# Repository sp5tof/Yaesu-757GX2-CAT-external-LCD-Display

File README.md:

# Yaesu-757GX2-CAT-external-LCD-Display
External HD77480 LCD display which shows up the transceiver status.
Arduino code, 3D case ready to print, Eagle schematic & board.
More Informations you can find at http://sp5tof.qrz.pl .

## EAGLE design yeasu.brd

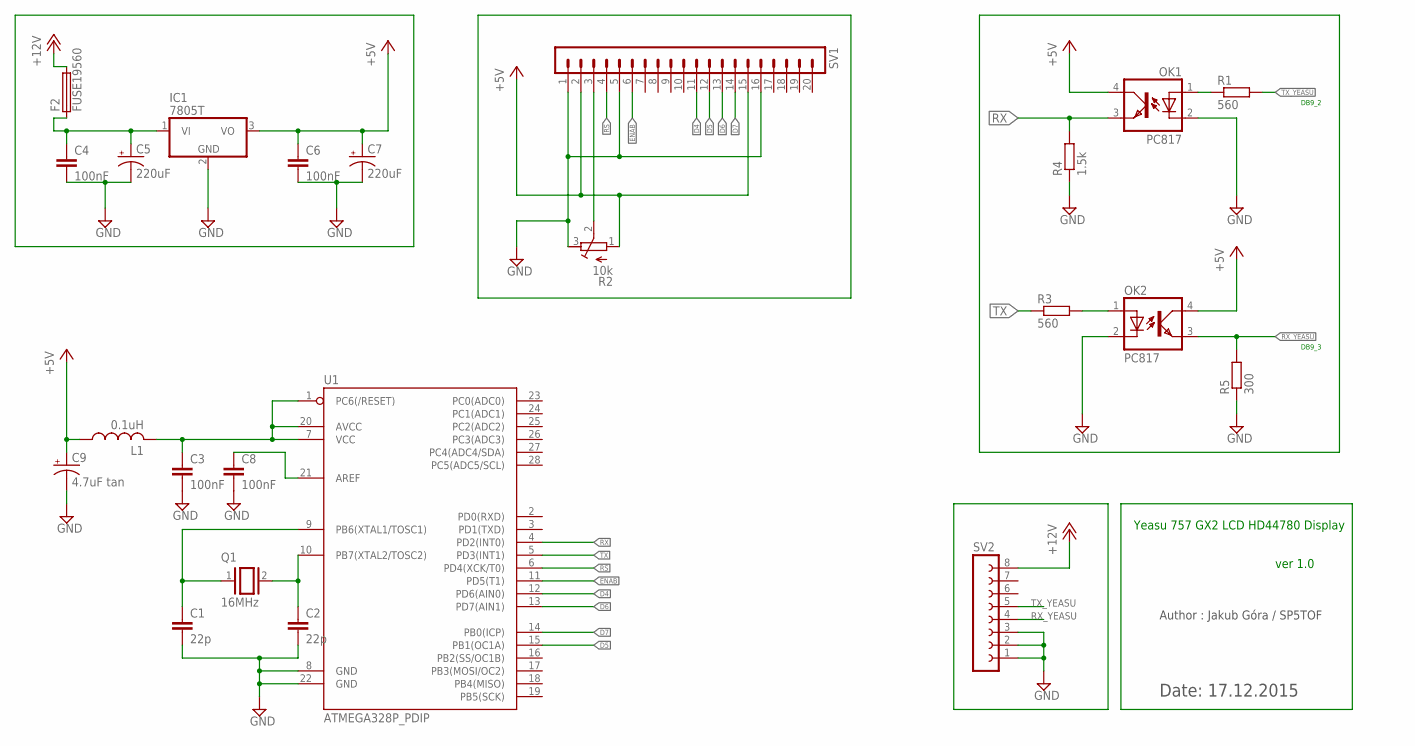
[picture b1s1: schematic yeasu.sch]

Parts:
C1, C2: 22p; C050-024X044
C3, C4, C6, C8: 100nF; C050-024X044
C5, C7: 220uF; CPOL-RADIAL-1000UF-63V
C9: 4.7uF tan; E2,5-6E
F2: FUSE19560; 19560
IC1: 7805T; TO220H
L1: 0.1uH; 0207/7
OK1, OK2: PC817; DIL04
Q1: 16MHz; QS
R1, R3: 560; 0207/10
R2: 10k; RTRIM3339P
R4: 1.5k; 0207/10
R5: 300; 0207/10
SV1: MA20-1
SV2: FE08-1; FE08
U1: ATMEGA328P_PDIP; DIL28-3

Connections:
+5V: C6.1, C7.1 (+), C9.+, IC1.3 (VO), L1.1, OK1.4 (COL), OK2.4 (COL), R2.1 (E), SV1.2, SV1.15
+12V: F2.2, SV2.8
D4: SV1.11, U1.12 (PD6(AIN0))
D5: SV1.12, U1.15 (PB1(OC1A))
D6: SV1.13, U1.13 (PD7(AIN1))
D7: SV1.14, U1.14 (PB0(ICP))
ENAB: SV1.6, U1.11 (PD5(T1))
GND: C1.2, C2.2, C3.2, C4.2, C5.2 (-), C6.2, C7.2 (-), C8.2, C9.-, IC1.2 (GND), OK1.2 (C), OK2.2 (C), R2.3 (A), R4.1, R5.1, SV1.1, SV1.5, SV1.16, SV2.1, SV2.2, SV2.3, U1.8 (GND), U1.22 (GND)
unnamed: OK1.1 (A), R1.1
unnamed: OK2.1 (A), R3.2
unnamed: C1.1, Q1.1, U1.9 (PB6(XTAL1/TOSC1))
unnamed: C2.1, Q1.2, U1.10 (PB7(XTAL2/TOSC2))
unnamed: C4.1, C5.1 (+), F2.1, IC1.1 (VI)
unnamed: C8.1, U1.21 (AREF)
unnamed: C3.1, L1.2, U1.1 (PC6(/RESET)), U1.7 (VCC), U1.20 (AVCC)
unnamed: R2.2 (S), SV1.3
RS: SV1.4, U1.6 (PD4(XCK/T0))
RX: OK1.3 (EMIT), R4.2, U1.4 (PD2(INT0))
RX_YEASU: OK2.3 (EMIT), R5.2, SV2.4
TX: R3.1, U1.5 (PD3(INT1))
TX_YEASU: R1.2, SV2.5

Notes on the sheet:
Yeasu 757 GX2 LCD HD44780 Display
ver 1.0
Author : Jakub Góra / SP5TOF
Date: 17.12.2015
DB9_2
DB9_3

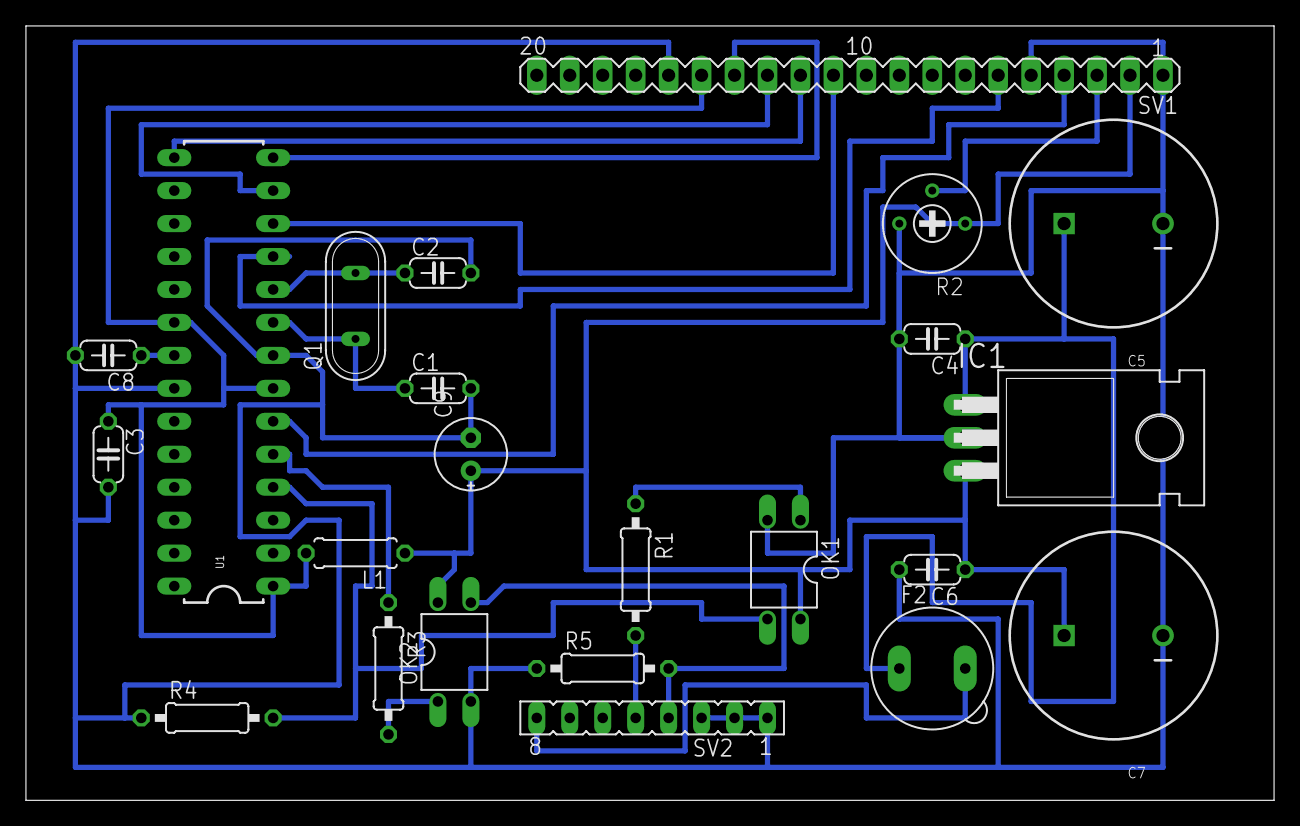
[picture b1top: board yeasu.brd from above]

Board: 2 copper layers, 96.2 x 59.7 mm, 23 parts (0 on the bottom side), 21 nets.

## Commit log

2025-01-07 Add files via upload
    Arduino code
2025-01-07 Add files via upload
    Customized libraries for Arduino code
2025-01-07 LCD chase project for 3D printing
2025-01-07 Add files via upload
    PCB project
2025-01-07 Add files via upload
    EAGLE schema
2025-01-07 Add files via upload
    Chase project
2025-01-07 Add files via upload
    STL chase project for 3D printing
2025-01-07 Add files via upload
    STL chase for 3D printing
2025-01-07 Add files via upload
    3D case - rear panel
2025-01-07 Add files via upload
    3D case for printing
2025-01-07 Add files via upload
    Eagle PCB board
2025-01-07 Add files via upload
    EAGLE PCB schema
2025-01-07 Add files via upload
    customized arduino libraries
2025-01-07 Add files via upload
    this is how it looks like
2025-01-07 Add files via upload
    Schema

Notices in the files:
parts and their libraries:
SparkFun-DigitalIC: Licensing: Creative Commons ShareAlike 4.0 International - https://creativecommons.org/licenses/by-sa/4.0
